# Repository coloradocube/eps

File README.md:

# eps
Expernal power supply board

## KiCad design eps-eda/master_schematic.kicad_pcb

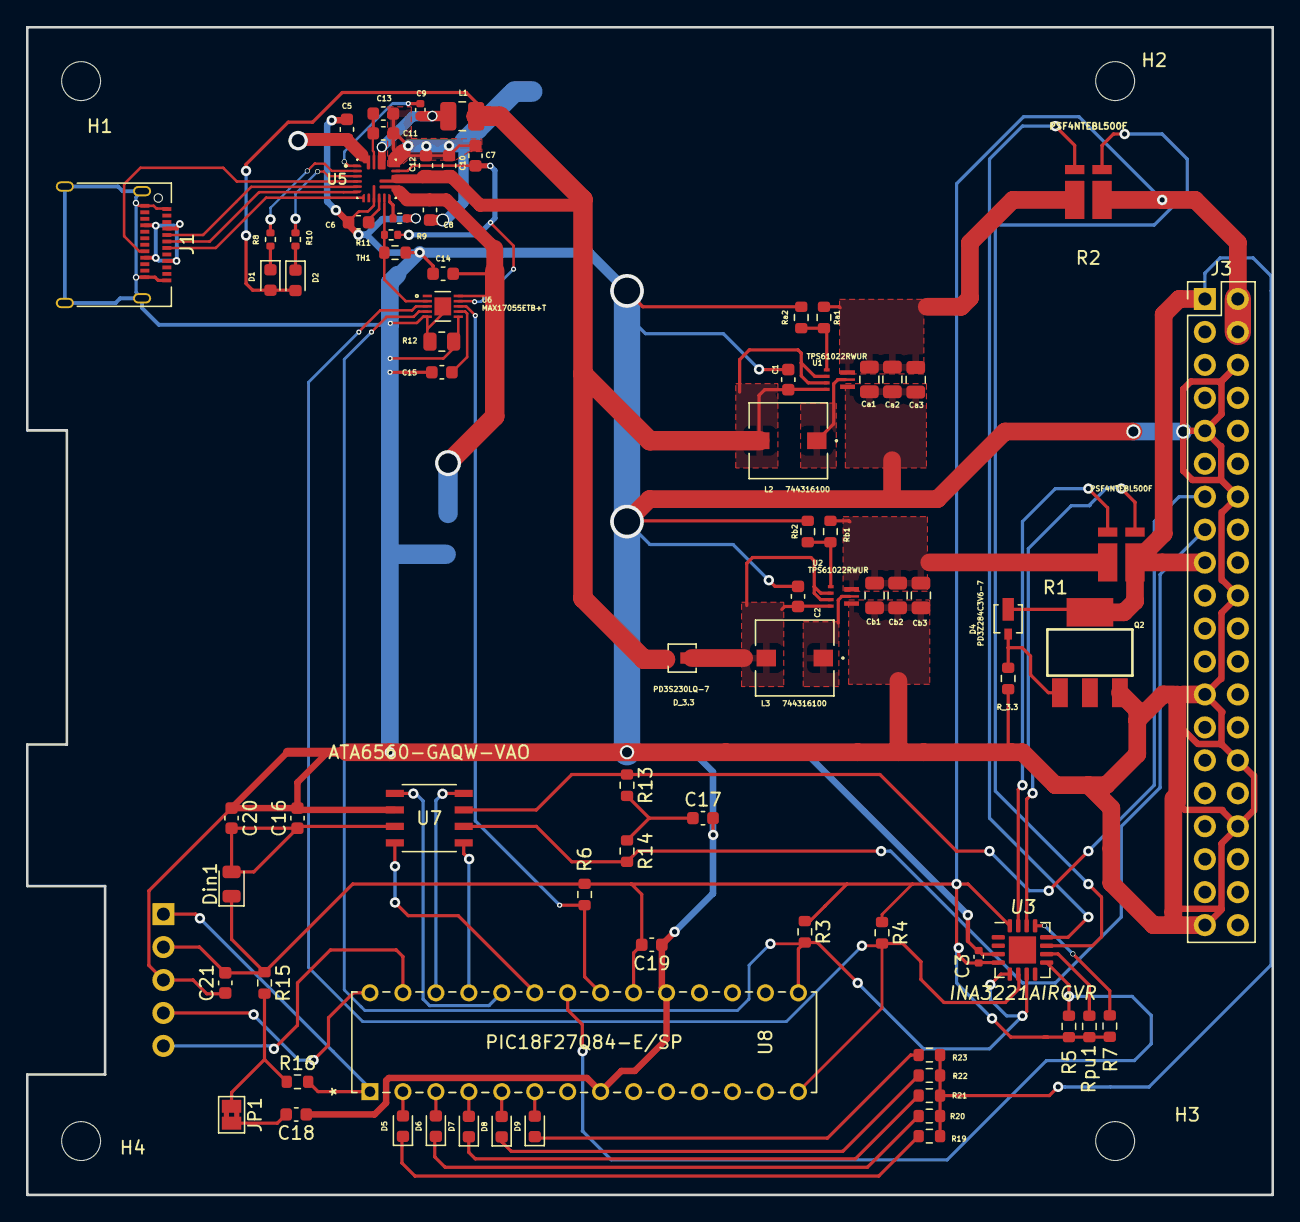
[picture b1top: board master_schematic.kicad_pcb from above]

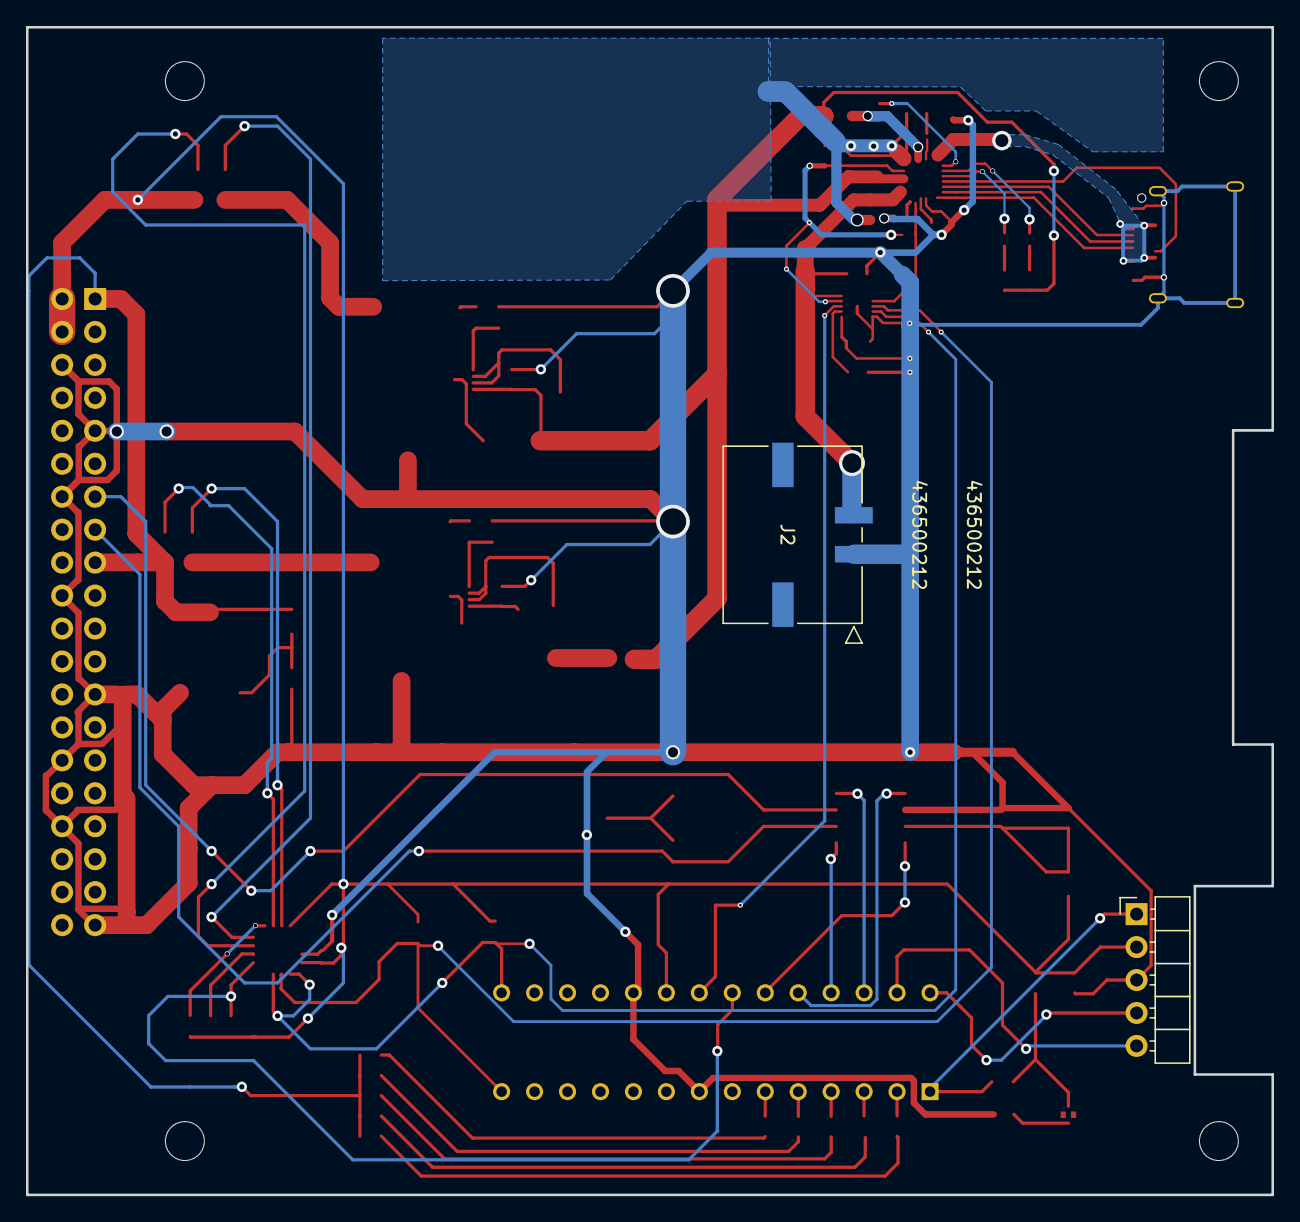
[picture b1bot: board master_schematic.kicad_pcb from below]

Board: 2 copper layers, 96.0 x 90.0 mm, 84 parts (2 on the bottom side), 64 nets.

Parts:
C1, C2, C8, C10, C11, C12: 10uF; C_0603_1608Metric
C3: 0.1μF; C_0402_1005Metric
C5, C6, C7: 2.2uF; C_0603_1608Metric
C9: 0.1uF; C_0402_1005Metric
C13, C20: 22uF; C_0603_1608Metric
C14, C18, C19, C21: 0.1uF; C_0603_1608Metric
C15: 0.47uF; C_0603_1608Metric
C16: 100nF; C_0603_1608Metric
C17: 4.7nF; C_0603_1608Metric
Ca1, Ca2, Ca3: 22uF; C_0805_2012Metric
Cb1, Cb2, Cb3: 22uF; C_0805_2012Metric
D1, D2: LED; LED_0603_1608Metric
D4: PD3Z284C3V6-7
D5: RED; LED_0603_1608Metric
D6: GREEN; LED_0603_1608Metric
D7, D8, D9: YELLOW; LED_0603_1608Metric
D_3.3: PD3S230LQ-7
Din1: DIODE; D_0805_2012Metric
H1, H2, H3, H4: 3mm_Mounting_Hole; MountingHole_3mm
J1: USB_C_Receptacle; USB_C_Receptacle_Amphenol_12401610E4-2A
J2: 436500212
J3: Conn_02x20_Odd_Even; PinHeader_2x20_P2.54mm_Vertical
J4: Conn_01x05_90deg; PinHeader_1x05_P2.54mm_Horizontal
JP1: SolderJumper_2_Open; SolderJumper-2_P1.3mm_Bridged2Bar_Pad1.0x1.5mm
L1: .47uH; L_1008_2520Metric
L2, L3: 744316100
Q2: FZT688BTA; SOT230P700X180-4N
R1, R2: PSF4NTEBL500F
R3, R4, R5, R6, R7: 10kΩ; R_0603_1608Metric
R8, R10: 1k; R_0402_1005Metric
R9: 24.9k; R_0402_1005Metric
R11: 10k; R_0402_1005Metric
R12: 0.010; R_0805_2012Metric
R13, R14: 60; R_0603_1608Metric
R15: 10k; R_0603_1608Metric
R16: 200; R_0603_1608Metric
R19, R20, R21, R22, R23: 330; R_0603_1608Metric
R_3.3: 1k; R_0603_1608Metric
Ra1: 732K; R_0603_1608Metric
Ra2: 100k; R_0603_1608Metric
Rb1: 453k; R_0603_1608Metric
Rb2: 100k; R_0603_1608Metric
Rpu1: 10kΩ; R_0603_1608Metric
TH1: 10k; R_0603_1608Metric
U1, U2: TPS61022RWUR
U3: INA3221AIRGVR; Texas_RGV_S-PVQFN-N16_EP2.1x2.1mm
U5: MAX77757JEFG435+; IC_MAX77757JEFG435+
U6: MAX17055ETB+T; MAX17055ETB&plus_T
U7: ATA6560-GAQW-VAO
U8: PIC18F27Q84-E/SP; PIC18F27Q84-E&slash_SP

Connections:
/ColoradoCUBE_Payload/3.3V: D4.1, J3.1, J3.17, Q2.4 (C), R1.4, R19.2, R20.2, R21.2, R22.2, R23.2
/ColoradoCUBE_Payload/5V: C3.1, C19.2, C21.2, Din1.1 (A), J3.2, J3.4, J4.2, R2.4, R3.1, R4.1, R5.1, R6.1, R7.1, R15.1, Rpu1.1, U3.4 (VS), U3.16 (VPU), U8.20 (VDD)
/ColoradoCUBE_Payload/ALRT: R6.2, U6.8 (ALRT), U8.21 (RB0)
/ColoradoCUBE_Payload/CANH: J3.13, R13.1, U7.7 (CANH)
/ColoradoCUBE_Payload/CANL: J3.15, R14.2, U7.6 (CANL)
/ColoradoCUBE_Payload/CAN_Transceiver/CAN_RX: U7.4 (RXD), U8.23 (RB2)
/ColoradoCUBE_Payload/CAN_Transceiver/CAN_TX: U7.1 (TXD), U8.24 (RB3)
/ColoradoCUBE_Payload/CAN_Transceiver/NSIL: U7.5 (NSIL), U8.25 (RB4)
/ColoradoCUBE_Payload/CAN_Transceiver/PWR: C16.1, C20.2, Din1.2 (K), U7.3 (VCC)
/ColoradoCUBE_Payload/CAN_Transceiver/STBY: U7.8 (STBY), U8.26 (RB5)
/ColoradoCUBE_Payload/CRT: R5.2, U3.9 (CRITICAL), U8.22 (RB1)
/ColoradoCUBE_Payload/ICSPC: J4.5, U8.27 (RB6/ICSPCLK)
/ColoradoCUBE_Payload/ICSPD: J4.4, U8.28 (RB7/ICSPDAT)
/ColoradoCUBE_Payload/LED_1: D5.2 (A), U8.2 (RA0)
/ColoradoCUBE_Payload/LED_2: D6.2 (A), U8.3 (RA1)
/ColoradoCUBE_Payload/LED_3: D7.2 (A), U8.4 (RA2)
/ColoradoCUBE_Payload/LED_4: D8.2 (A), U8.5 (RA3)
/ColoradoCUBE_Payload/LED_5: D9.2 (A), U8.6 (RA4)
/ColoradoCUBE_Payload/MCLR: J4.1, R16.2, U8.1 (*MCLR/VPP/RE3)
/ColoradoCUBE_Payload/SCL_RC3: R4.2, U3.6 (SCL), U6.3 (SCL), U8.14 (RC3)
/ColoradoCUBE_Payload/SDA_RC4: R3.2, U3.5 (A0), U3.7 (SDA), U6.4 (SDA), U8.15 (RC4)
/charge schem/SYSPOWER: C1.1, C10.1, C12.1, D1.2 (A), D2.2 (A), D_3.3.2 (EPAD), L1.2, L2.2, U1.5 (EN), U1.6 (MODE), U1.7 (VIN), U5.15_16 (SYS)
/charge schem/V_BAT: C8.1, C14.1, J2.2, U5.13_14 (BATT), U6.10 (BATT)
/converterschematic/PV: Rpu1.2, U3.10 (PV)
/converterschematic/TC: R7.2, U3.13 (TC)
GND: C1.2, C2.2, C3.2, C5.2, C6.2, C14.2, C15.2, C16.2, C17.2, C18.1, C19.1, C20.1, C21.1, Ca1.2, Ca2.2, Ca3.2, Cb1.2, Cb2.2, Cb3.2, J1.A1 (GND), J1.A12 (GND), J1.B1 (GND), J1.B12 (GND), J1.S1 (SHIELD), J2.1, J3.6, J3.9, J3.14, J3.20, J3.25, J3.30, J3.34, J3.39, J4.3, Q2.3 (E), R9.2, R12.1, R12.2, R_3.3.2, Ra2.2, Rb2.2, TH1.2, U1.1 (GND), U2.1 (GND), U3.3 (GND), U5.9 (GND), U6.5 (CSN), U6.6 (CSP), U6.11 (EPAD), U7.2 (GND), U8.8 (VSS), U8.19 (VSS)
GNDPWR: C7.2, C8.2, C10.2, C11.2, C12.2, C13.2, U5.18_19 (PGND)
unnamed: C5.1, J1.A4 (VBUS), J1.A9 (VBUS), J1.B4 (VBUS), J1.B9 (VBUS), U5.23_24 (CHGIN)
unnamed: C6.1, U5.10 (VDD)
unnamed: C7.1, R11.1, U5.17 (PVL), U6.9 (THRM)
unnamed: C9.1, U5.1 (BST)
unnamed: C9.2, L1.1, U5.20_21 (LX)
unnamed: C11.1, C13.1, U5.22 (BYP)
unnamed: C15.1, U6.7 (REG)
unnamed: C17.1, R13.2, R14.1
unnamed: C18.2, JP1.2 (B)
unnamed: Ca1.1, Ca2.1, Ca3.1, R2.1, Ra1.1, U1.3 (VOUT)
unnamed: Cb1.1, Cb2.1, Cb3.1, R1.1, Rb1.1, U2.3 (VOUT)
unnamed: D1.1 (K), R8.1
unnamed: D2.1 (K), R10.1
unnamed: D4.2, Q2.1 (B), R_3.3.1
unnamed: D5.1 (K), R19.1
unnamed: D6.1 (K), R20.1
unnamed: D7.1 (K), R21.1
unnamed: D8.1 (K), R22.1
unnamed: D9.1 (K), R23.1
unnamed: C2.1, D_3.3.1 (EPAD), L3.2, U2.5 (EN), U2.6 (MODE), U2.7 (VIN)
unnamed: J1.A5 (CC1), U5.5 (CC1)
unnamed: J1.A6 (D+), U5.6 (DP)
unnamed: J1.A7 (D-), U5.7 (DN)
unnamed: J1.B5 (CC2), U5.4 (CC2)
unnamed: JP1.1 (A), R15.2, R16.1
unnamed: L2.1, U1.2 (SW)
unnamed: L3.1, U2.2 (SW)
unnamed: R1.2, U3.15 (IN+2)
unnamed: R1.3, U3.14 (IN-2)
unnamed: R2.2, U3.12 (IN+1)
unnamed: R2.3, U3.11 (IN-1)
unnamed: R8.2, U5.2 (INOKB)
unnamed: R9.1, U5.12 (IFAST)
unnamed: R10.2, U5.3 (STAT)
unnamed: R11.2, TH1.1, U5.11 (THM), U6.2 (AIN)
unnamed: Ra1.2, Ra2.1, U1.4 (FB)
unnamed: Rb1.2, Rb2.1, U2.4 (FB)

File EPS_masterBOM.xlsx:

; | /Users/sethschisler/eps/eps-eda/master_schematic.kicad_sch
Date: | Monday, April 25, 2022 at 09:28:04 AM
Tool: | Eeschema (6.0.1-0)
Generator: | /Applications/KiCad/KiCad.app/Contents/SharedSupport/plugins/bom_csv_grouped_by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
Component Count: | 80
Ref | Qnty | Value | Cmp name | Footprint | Description | Vendor
C1, C2, C8, C10, C11, C12, | 6 | 10uF | C_Small | Capacitor_SMD:C_0603_1608Metric | Unpolarized capacitor, small symbol
C3, | 1 | 0.1ŒºF | C_Small | Capacitor_SMD:C_0402_1005Metric | Unpolarized capacitor, small symbol
C5, C6, C7, | 3 | 2.2uF | C_Small | Capacitor_SMD:C_0603_1608Metric | Unpolarized capacitor, small symbol
C9, | 1 | 0.1uF | C_Small | Capacitor_SMD:C_0402_1005Metric | Unpolarized capacitor, small symbol
C13, C20, | 2 | 22uF | C | Capacitor_SMD:C_0603_1608Metric | Unpolarized capacitor
C14, C18, C19, C21, | 4 | 0.1uF | C | Capacitor_SMD:C_0603_1608Metric | Unpolarized capacitor
C15, | 1 | 0.47uF | C_Small | Capacitor_SMD:C_0603_1608Metric | Unpolarized capacitor, small symbol
C16, | 1 | 100nF | C | Capacitor_SMD:C_0603_1608Metric | Unpolarized capacitor
C17, | 1 | 4.7nF | C | Capacitor_SMD:C_0603_1608Metric | Unpolarized capacitor
Ca1, Ca2, Ca3, | 3 | 22uF | C_Small | Capacitor_SMD:C_0805_2012Metric | Unpolarized capacitor, small symbol
Cb1, Cb2, Cb3, | 3 | 22uF | C_Small | Capacitor_SMD:C_0805_2012Metric | Unpolarized capacitor, small symbol
D1, D2, | 2 | LED | LED | LED_SMD:LED_0603_1608Metric | Light emitting diode
D4, | 1 | PD3Z284C3V6-7 | PD3Z284C3V6-7 | zener_ovp:PD3Z284C3V6-7
D5, | 1 | RED | LED_Small_Filled | LED_SMD:LED_0603_1608Metric | Light emitting diode, small symbol, filled shape
D6, | 1 | GREEN | LED_Small_Filled | LED_SMD:LED_0603_1608Metric | Light emitting diode, small symbol, filled shape
D7, D8, D9, | 3 | YELLOW | LED_Small_Filled | LED_SMD:LED_0603_1608Metric | Light emitting diode, small symbol, filled shape
D_3.3, | 1 | PD3S230LQ-7 | PD3S230LQ-7 | footprints3:PD3S230LQ-7
Din1, | 1 | DIODE | DIODE | Diode_SMD:D_0805_2012Metric | Diode, anode on pin 1, for simulation only!
J1, | 1 | USB_C_Receptacle | USB_C_Receptacle | Connector_USB:USB_C_Receptacle_Amphenol_12401610E4-2A | USB Full-Featured Type-C Receptacle connector
J2, | 1 | 436500212 | 436500212 | molex connector:436500212
J3, | 1 | Conn_02x20_Odd_Even | Conn_02x20_Odd_Even | Connector_PinHeader_2.54mm:PinHeader_2x20_P2.54mm_Vertical | Generic connector, double row, 02x20, odd/even pin numbering scheme (row 1 odd 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
J4, | 1 | Conn_01x05_90deg | Conn_01x05_Female | Connector_PinHeader_2.54mm:PinHeader_1x05_P2.54mm_Horizontal | Generic connector, single row, 01x05, script generated (kicad-library-utils/sch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
JP1, | 1 | SolderJumper_2_Open | SolderJumper_2_Open | Jumper:SolderJumper-2_P1.3mm_Bridged2Bar_Pad1.0x1.5mm | Solder Jumper, 2-pole, open
L1, | 1 | .47uH | L_Small | Inductor_SMD:L_1008_2520Metric | Inductor, small symbol
L2, L3, | 2 | 744316100 | 744316100 | footprints1:744316100
Q2, | 1 | FZT688BTA | 2N2219 | fzt688bta_footprint:SOT230P700X180-4N | 800mA Ic, 50V Vce, NPN Transistor, TO-39
R1, R2, | 2 | PSF4NTEBL500F | PSF4NTEBL500F | psf4nt:PSF4NTEBL500F
R3, R4, R5, R6, R7, | 5 | 10kŒ© | R_Small_US | Resistor_SMD:R_0603_1608Metric | Resistor, small US symbol
R8, R10, | 2 | 1k | R_Small_US | Resistor_SMD:R_0402_1005Metric | Resistor, small US symbol
R9, | 1 | 24.9k | R_Small_US | Resistor_SMD:R_0402_1005Metric | Resistor, small US symbol
R11, | 1 | 10k | R_Small_US | Resistor_SMD:R_0402_1005Metric | Resistor, small US symbol
R12, | 1 | 0.01 | R_Small_US | Resistor_SMD:R_0805_2012Metric | Resistor, small US symbol
R13, R14, | 2 | 60 | R | Resistor_SMD:R_0603_1608Metric | Resistor
R15, | 1 | 10k | R | Resistor_SMD:R_0603_1608Metric | Resistor
R16, | 1 | 200 | R | Resistor_SMD:R_0603_1608Metric | Resistor
R19, R20, R21, R22, R23, | 5 | 330 | R | Resistor_SMD:R_0603_1608Metric | Resistor
R_3.3, | 1 | 1k | R_Small_US | Resistor_SMD:R_0603_1608Metric | Resistor, small US symbol
Ra1, | 1 | 732K | R_Small_US | Resistor_SMD:R_0603_1608Metric | Resistor, small US symbol
Ra2, | 1 | 100k | R_Small_US | Resistor_SMD:R_0603_1608Metric | Resistor, small US symbol
Rb1, | 1 | 453k | R_Small_US | Resistor_SMD:R_0603_1608Metric | Resistor, small US symbol
Rb2, | 1 | 100k | R_Small_US | Resistor_SMD:R_0603_1608Metric | Resistor, small US symbol
Rpu1, | 1 | 10kŒ© | R_Small_US | Resistor_SMD:R_0603_1608Metric | Resistor, small US symbol
TH1, | 1 | 10k | Thermistor_NTC | Resistor_SMD:R_0603_1608Metric | Temperature dependent resistor, negative temperature coefficient
U1, U2, | 2 | TPS61022RWUR | TPS61022RWUR | footprints:TPS61022RWUR
U3, | 1 | INA3221AIRGVR | INA3221 | Package_DFN_QFN:Texas_RGV_S-PVQFN-N16_EP2.1x2.1mm | Triple-Channel High-Side Shunt and Bus Voltage Monitor with I2C and SMBUS Compa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
U5, | 1 | MAX77757JEFG435+ | MAX77757JEFG435+ | max77757:IC_MAX77757JEFG435+
U6, | 1 | MAX17055ETB+T | MAX17055ETB+T | max17055 smd:MAX17055ETB&plus_T
U7, | 1 | ATA6560-GAQW-VAO | ATA6560-GAQW-VAO | ata6560:ATA6560-GAQW-VAO
U8, | 1 | PIC18F27Q84-E/SP | PIC18F27Q84-E{slash}SP | pic18f27:PIC18F27Q84-E&slash_SP

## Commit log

2022-04-21 first separate eps commit
2022-04-22 rev 0.2 update
    added 90deg pic adapter to include an edge cutout.
    changed footprint of fuel gauge to implement ALRT signal.
    rotated battery connector to better implement with the battery board.
2022-04-22 purged unnecessary files
2022-04-23 EPS V0.2
    Adjusted placement of resistors R19 through R23, and capacitor C18. For mounting purposes. Most DRC errors have now been cleared.
2022-04-23 EPS V0.2 quick update
    added schottyky diode before 3.3V boost converter
2022-04-23 EPS V0.3
    Added over voltage protection system for the 3.3V rail.
2022-04-25 rev 0.2
    ran DRC with updated board. rev0.2 complete
2022-04-25 EPS BOM
2022-04-28 bom directory
2022-05-04 minor bom touchup
2022-05-04 eps gerbers for jlcpcb
2022-05-04 ignore excel, zip
2022-05-04 remove zip
2022-05-10 cleanup
2022-05-10 cleanup of archives
2022-05-10 cleanup archives
2022-05-10 student BOM minor edits
2022-05-13 convert to JLC BOM format
2022-05-13 JLC part number or order source
2022-05-13 BOM as of 2022-05-13
2022-05-13 Saving BOM for education
    Sample-BOM_JLCSMT contains the JLCPCB format. eps-bom-kicad-6-default is the default BOM export for the eps by KiCAD 6.0.2. eps_BOM contains 2 drafts and a finished sheet of the JLC-formatted BOM, wi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
2022-05-13 Links to the out-of-stock parts

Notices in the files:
parts and their libraries:
Copyright 2021 Accelerated Designs. All rights reserved.
